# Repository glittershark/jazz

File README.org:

#+title: jazz

some daisy seed effect pedal firmware

run ~nix-shell~ to get dependencies. see [[https://github.com/glittershark/jazz/blob/main/shell.nix][shell.nix]] for a list of dependencies if
you are less of a nix weenie than i am

* building and testing

be sure to check out all the submodules:
#+begin_src shell-session
$ git submodule update --init --recursive
#+end_src

to build firmware blobs for all effects:

#+begin_src shell-session
$ make
#+end_src

to run tests:

#+begin_src shell-session
$ make test
#+end_src

~compile_commands.json~ is automatically merged from both ARM and host builds into the project root for clangd/language server support.

* host audio CLI

for quick iteration without flashing firmware, the host CLI lets you run effects
on mp3 files from your computer.

** quick start

build the host CLI:

#+begin_src shell-session
$ make console
#+end_src

run input through the default effect (~granular~) and play through your computer:

#+begin_src shell-session
$ ./build-test/src/console/jazz-console input.mp3
#+end_src

save processed output to a new mp3:

#+begin_src shell-session
$ ./build-test/src/console/jazz-console input.mp3 --output processed.mp3
#+end_src

output filenames default to the ~mp3s/~ folder in the current directory (created
if needed), so this writes ~mp3s/processed.mp3~ when run from the repo root.
explicit paths such as ~./processed.mp3~ or ~/tmp/processed.mp3~ are used as given.

if the output already exists, choose ~n~ to append the first available number
(~processed_1.mp3~, ~processed_2.mp3~, ...), ~o~ to overwrite, or ~c~ to cancel.
Enter or end-of-input cancels with a nonzero exit status before playback or
rendering starts. overwriting the input file itself is rejected; choose a
numbered filename instead.

if playback fails on your machine, disable playback and render offline:

#+begin_src shell-session
$ ./build-test/src/console/jazz-console input.mp3 --no-play --output processed.mp3
#+end_src

** effects and chains

list available effects:

#+begin_src shell-session
$ ./build-test/src/console/jazz-console --list-effects
#+end_src

select one effect:

#+begin_src shell-session
$ ./build-test/src/console/jazz-console input.mp3 --effect clip
#+end_src

try the fridge terminal preset:

#+begin_src shell-session
$ ./build-test/src/console/jazz-console input.mp3 --preset presets/host/fridge_demo.toml --output fridge_demo.mp3
#+end_src

try the standalone la sort demo (the same sorting engine runs on the Daisy):

#+begin_src shell-session
$ ./build-test/src/console/jazz-console input.mp3 --preset presets/host/la_sort_demo.toml --output la_sort_demo.mp3
#+end_src

add ~--no-play~ to render offline. for a fully wet version or a different rank:

#+begin_src shell-session
$ ./build-test/src/console/jazz-console input.mp3 --preset presets/host/la_sort_demo.toml --la-sort-dry 0 --la-sort-wet 1 --la-sort-weight-center 0.65
#+end_src

la sort keeps the MP3's left and right channels separate. see
[[file:src/la_sort/README.md][the la sort guide]] for controls and firmware details.

inspect the fridge preset's LFO motion without rendering audio:

#+begin_src shell-session
$ ./build-test/src/console/jazz-console --preset presets/host/fridge_demo.toml --fridge-lfo-chart
#+end_src

render that LFO motion as a matplotlib image:

#+begin_src shell-session
$ python scripts/plot_fridge_lfo.py --preset presets/host/fridge_demo.toml --output fridge_lfo.png
#+end_src

chain multiple effects in order:

#+begin_src shell-session
$ ./build-test/src/console/jazz-console input.mp3 --effect clip,lowpass,granular
#+end_src

** effect parameters

you can tune parameters from the command line:

#+begin_src shell-session
$ ./build-test/src/console/jazz-console input.mp3 --effect clip,la_sort --clip-threshold 0.2 --la-sort-weight-center 0.65
#+end_src

supported parameter flags:
- ~--clip-threshold~, ~--clip-gain~
- ~--anticlip-threshold~, ~--anticlip-gain~
- ~--lowpass-alpha~, ~--highpass-alpha~
- ~--cursed-lowpass-alpha~, ~--cursed-highpass-alpha~
- ~--la-sort-weight-center~, ~--la-sort-weight-sharpness~
- ~--la-sort-dry~, ~--la-sort-wet~
- ~--la-sort-length~: integer 1–1024 samples, default 64; preset key ~la_sort_length~
- ~--la-sort-volume-compensation~: 0–1, default 1; fixed sqrt(length) wet gain, up to +30 dB at 1024 (no dynamics control)
- ~--la-sort-lfo-rate~: 0.05–20 Hz, default 1; ~--la-sort-lfo-depth~: 0–1, default 0 (off), 1 sweeps the whole list

the fridge effect is configured through preset keys with the prefixes
~fridge_head_N_~ and ~fridge_lfo_N_~; see ~presets/host/fridge_demo.toml~.

** presets (toml/json)

load a preset file:

#+begin_src shell-session
$ ./build-test/src/console/jazz-console input.mp3 --preset presets/host/clip_lasort.toml --output processed.mp3
#+end_src

example presets included in repo:
- ~presets/host/fridge_demo.toml~
- ~presets/host/la_sort_demo.toml~
- ~presets/host/clip_lasort.toml~

CLI flags override preset values, so you can start from a preset and tweak:

#+begin_src shell-session
$ ./build-test/src/console/jazz-console input.mp3 --preset presets/host/clip_lasort.toml --clip-threshold 0.1
#+end_src

JSON preset example:

#+begin_src shell-session
$ cat > /tmp/example_preset.json <<'EOF'
{
  "effect_chain": ["clip", "la_sort", "highpass"],
  "clip_threshold": 0.3,
  "clip_gain": 10.0,
  "la_sort_weight_center": 0.62,
  "la_sort_weight_sharpness": 4.0,
  "highpass_alpha": 0.2
}
EOF
$ ./build-test/src/console/jazz-console input.mp3 --preset /tmp/example_preset.json --output processed.mp3
#+end_src

the CLI depends on ~ffmpeg~ and ~ffplay~ being available in your shell.

* flashing to daisy seed

to flash a particular effect to a daisy seed via STLink:

#+begin_src shell-session
$ make flash DIR=delay
#+end_src

or manually:

#+begin_src shell-session
$ st-flash write build/src/delay/delay.bin 0x08000000
$ st-flash reset
#+end_src

* printing stuff

see [[https://github.com/glittershark/jazz/blob/main/src/console/console.cpp][console]] for how to set up the console. reading from it should be something
like ~screen /dev/ttyACM0 115200~.

* current effects

** delays
- [[https://github.com/glittershark/jazz/blob/main/src/delay/delay.cpp][delay]]: literally just a perfectly clean delay.
- [[https://github.com/glittershark/jazz/blob/main/src/reverse/reverse.cpp][reverse]]: a simple reverse delay.
- [[https://github.com/glittershark/jazz/blob/main/src/granular/granular.cpp][granular]]: weird semi-generative granular delay.
- [[https://github.com/glittershark/jazz/tree/main/src/rachel][rachel]]: heavily modulated multi-delay

** filters
- [[https://github.com/glittershark/jazz/blob/main/src/low_pass_filter/lowpass_filter.cpp][low_pass_filter]]: simple one-pole lowpass filter.
- [[https://github.com/glittershark/jazz/blob/main/src/high_pass_filter/highpass_filter.cpp][high_pass_filter]]: simple one-pole highpass filter.
- [[https://github.com/glittershark/jazz/blob/main/src/cursed_low_pass_filter/cursed_lowpass_filter.cpp][cursed_low_pass_filter]]: cursed lowpass filter using exponentiation and multiplication.
- [[https://github.com/glittershark/jazz/blob/main/src/cursed_high_pass_filter/cursed_highpass_filter.cpp][cursed_high_pass_filter]]: cursed highpass filter using exponentiation and multiplication.

** distortion
- [[https://github.com/glittershark/jazz/blob/main/src/clip/clip.cpp][clip]]: hard clipping distortion.
- [[https://github.com/glittershark/jazz/blob/main/src/anticlip/anticlip.cpp][anticlip]]: adds back the residue from clipping.

** other
- [[file:src/la_sort/README.md][la_sort]]: stereo sorting-based effect with a weighted tap from a configurable rolling window (default 64 samples), shared by firmware and the MP3 demo.

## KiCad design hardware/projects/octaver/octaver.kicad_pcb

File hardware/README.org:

#+title: README (hardware)

* directory structure
- =projects/=: kicad projects
  - =devboard/=: general development board
  - =octaver/=: the can
- =lib/=: library files
  - =kicad/=: kicad part library files
    - =custom.kicad_sym=: custom symbol library (stuff we've drawn)
    - =custom.pretty/=: custom footprint library (stuff we've drawn)
    - =vendor/=: symbol library files (=*.kicad_sym=) downloaded from vendors
    - =vendor.pretty/=: footprint files (=*.kicad_mod=) & 3D models downloaded from vendors
  - =spice/=: spice simulation files
* creating a new project
1. create it in kicad under =projects/=
2. copy == & == from this directory into the project; this pulls in our custom
   libraries with all our stuff
3. enjoy!
* adding downloaded symbols & footprints
1. download the symbol & footprint libraries for the latest version of kicad
   available (6+ is fine)
2. move files:
   a. =*.kicad_sym= -> =lib/kicad/vendor/=
   b. =*.kicad_mod=, 3D models -> =lib/kicad/vendor.pretty/=
3. open the symbol editor. for each new symbol, change the footprint reference
   to =vendor:*= (since we just put the footprint into our own library)
4. open the footprint editor: for each new referenced footprint, if it should
   have a 3D model associated with it (i.e., the library came with a model),
   ensure the model shows up in the 3D view of the footprint. if not, add it and
   move it to the right place.

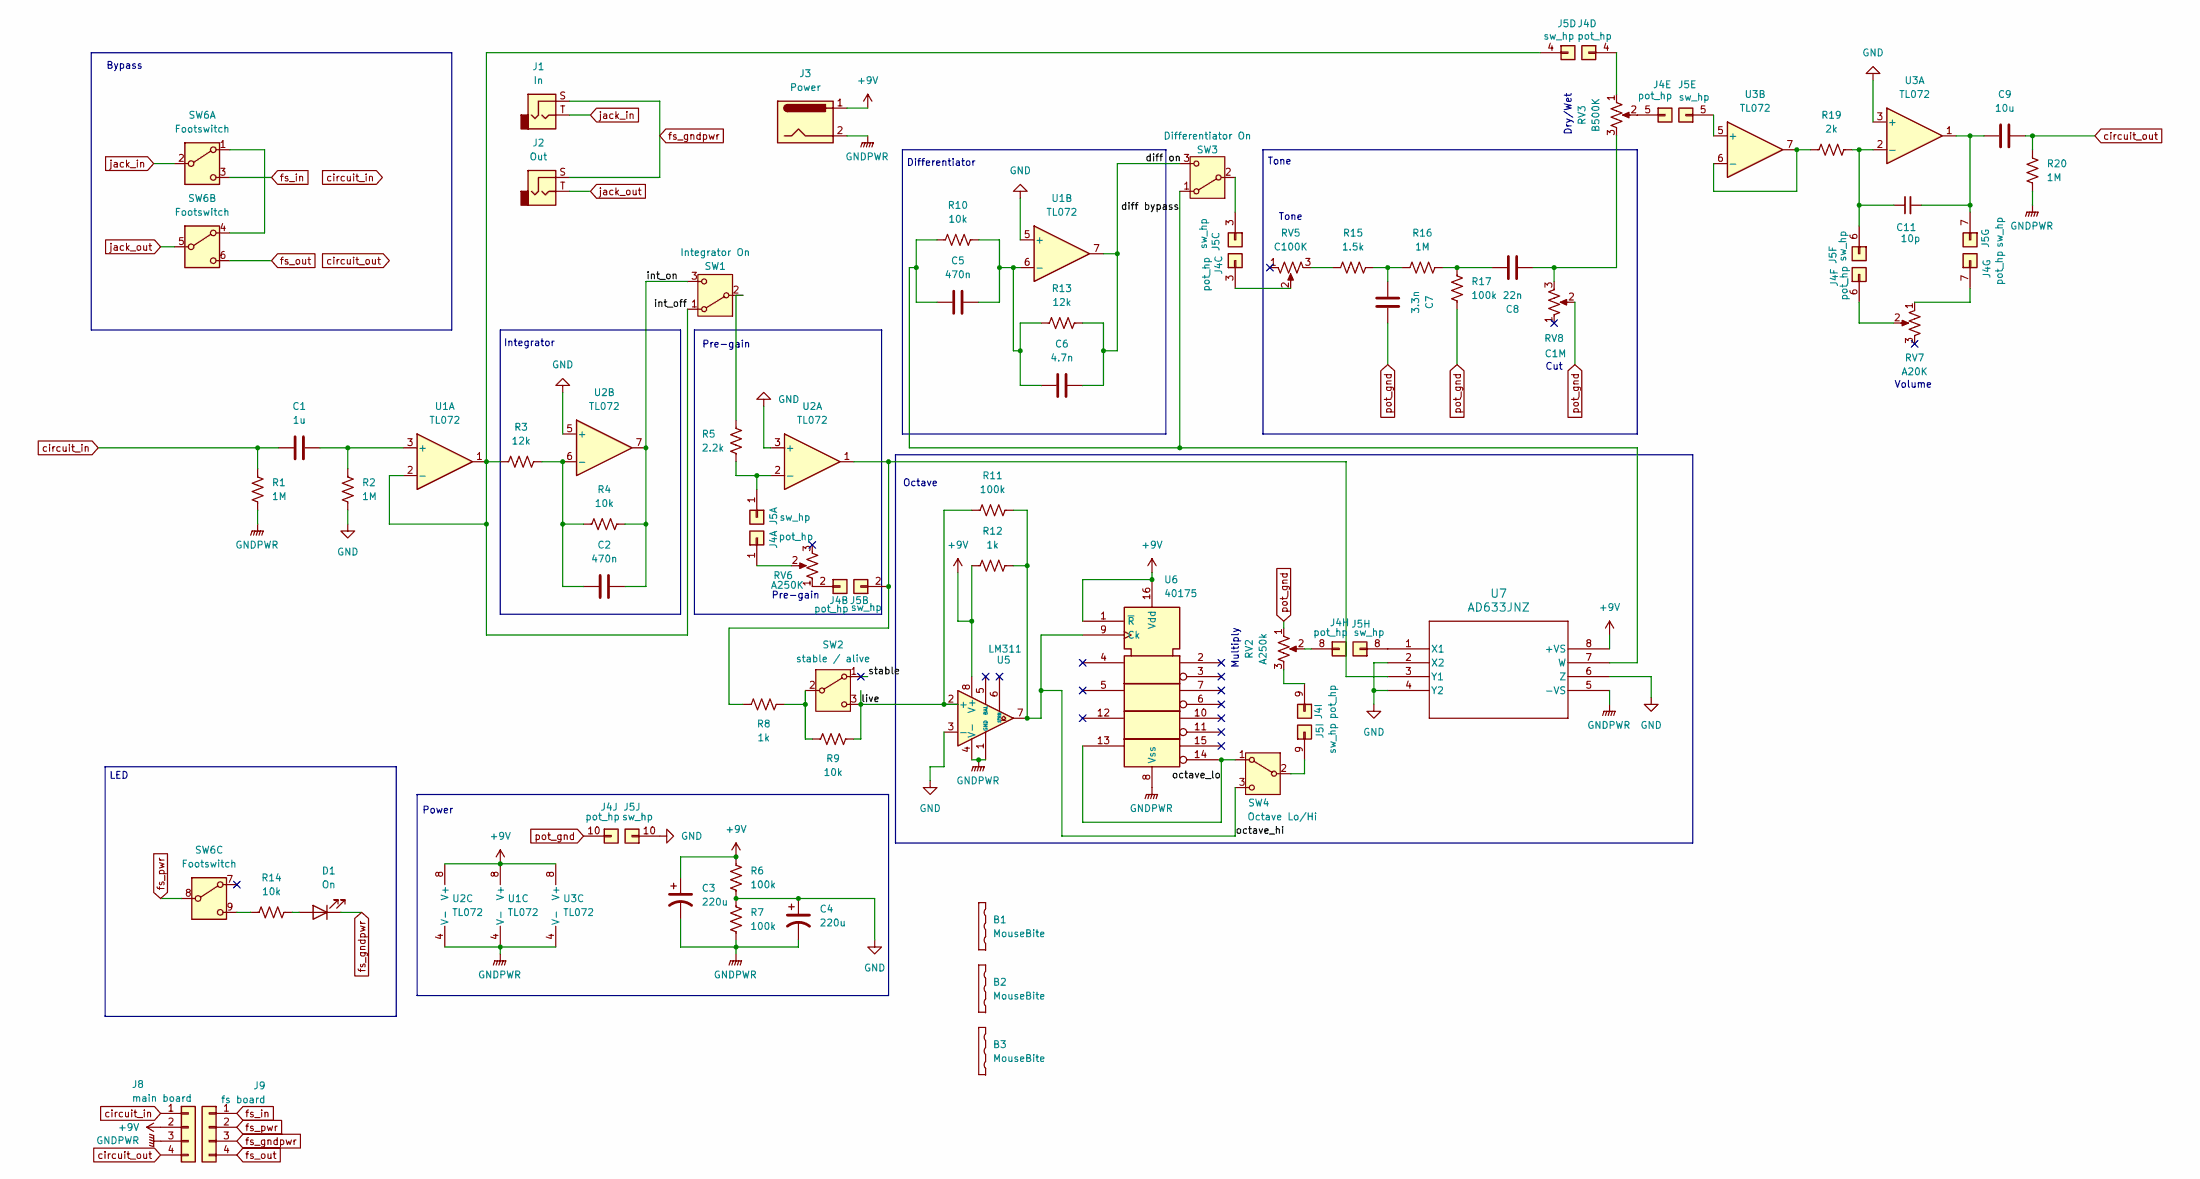
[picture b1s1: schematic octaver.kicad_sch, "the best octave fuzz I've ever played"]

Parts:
B1, B2, B3: MouseBite; MouseBite_2.54x7.62mm_JLCPCB
C1: 1u; C_0603_1608Metric; LCSC C15849
C2, C5: 470n; C_0603_1608Metric; LCSC C1623
C3, C4: 220u; CP_Elec_8x10.5; LCSC C3340
C6: 4.7n; C_0603_1608Metric; LCSC C53987
C7: 3.3n; C_0603_1608Metric; LCSC C1613
C8: 22n; C_0603_1608Metric; LCSC C21122
C9: 10u; C_0603_1608Metric; LCSC C96446
C11: 10p; C_0603_1608Metric; LCSC C1634
D1: On; LED_D5.0mm
J1: In; mono_jack
J2: Out; mono_jack
J3: Power; PinHeader_1x02_P2.54mm_Vertical
J4: pot_hp; PinHeader_1x10_P2.54mm_Vertical
J5: sw_hp; PinHeader_1x10_P2.54mm_Vertical
J8: main board; PinHeader_1x04_P2.54mm_Vertical
J9: fs board; PinHeader_1x04_P2.54mm_Vertical
R1, R2, R16, R20: 1M; R_0402_1005Metric; LCSC C26083
R3, R13: 12k; R_0402_1005Metric; LCSC C25752
R4, R9, R10: 10k; R_0402_1005Metric; LCSC C25744
R5: 2.2k; R_0402_1005Metric; LCSC C25879
R6, R7, R11, R17: 100k; R_0402_1005Metric; LCSC C25741
R8, R12: 1k; R_0402_1005Metric; LCSC C11702
R14: 10k; R_Axial_DIN0207_L6.3mm_D2.5mm_P10.16mm_Horizontal
R15: 1.5k; R_0402_1005Metric; LCSC C25867
R19: 2k; R_0402_1005Metric; LCSC C4109
RV2: A250k; Taiss_Potentiometer_vertical
RV3: B500K; Taiss_Potentiometer_vertical
RV5: C100K; Taiss_Potentiometer_vertical
RV6: A250K; Taiss_Potentiometer_vertical
RV7: A20K; Taiss_Potentiometer_vertical
RV8: C1M; Taiss_Potentiometer_vertical
SW1: Integrator On; Adam Tech SW-T3-2B-A-A3-S1
SW2: stable / alive; Adam Tech SW-T3-2B-A-A3-S1
SW3: Differentiator On; Adam Tech SW-T3-2B-A-A3-S1
SW4: Octave Lo/Hi; Adam Tech SW-T3-2B-A-A3-S1
SW6: Footswitch; PBS-24-302_3PDT
U1, U2, U3: TL072; SOIC-8_3.9x4.9mm_P1.27mm; LCSC C6961
U5: LM311; SOIC-8_3.9x4.9mm_P1.27mm; LCSC C7939
U6: 40175; SOIC-16W_5.3x10.2mm_P1.27mm; LCSC C1549824
U7: AD633JNZ; DIP-8_W7.62mm

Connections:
+9V: C3.1, J3.1, J8.2, R6.2, R12.2, U1.8 (V+), U2.8 (V+), U3.8 (V+), U5.8 (V+), U6.1 (~R), U6.16 (Vdd), U7.8 (+VS)
/diff bypass: C5.2, R10.2, SW3.1 (A), U7.7 (W)
/diff on: C6.1, R13.1, SW3.3 (C), U1.7
/int_off: J5.4 (Pin_3), R3.2, SW1.1 (A), U1.1, U1.2 (-)
/int_on: C2.1, R4.1, SW1.3 (C), U2.7
/live: R9.2, R11.2, SW2.3 (C), U5.2 (+)
/octave_hi: R11.1, R12.1, SW4.3 (C), U5.7, U6.9 (Ck)
/octave_lo: SW4.1 (A), U6.13, U6.14
/stable: SW2.1 (A)
GND: C4.1, J5.10 (Pin_3), R2.1, R6.1, R7.2, U1.5 (+), U2.3 (+), U2.5 (+), U3.3 (+), U5.3 (-), U7.2 (X2), U7.4 (Y2), U7.6 (Z)
GNDPWR: C3.2, C4.2, J3.2, J8.3, R1.1, R7.1, R20.1, U1.4 (V-), U2.4 (V-), U3.4 (V-), U5.1 (GND), U5.4 (V-), U6.8 (Vss), U7.5 (-VS)
unnamed: C7.2, R15.1, R16.2
unnamed: C8.1, R16.1, R17.2
unnamed: C8.2, RV3.3, RV8.3
unnamed: D1.2 (A), R14.1
unnamed: J4.1 (Pin_3), RV6.2
unnamed: J4.2, RV6.1
unnamed: J4.3, RV5.2
unnamed: J4.4 (Pin_3), RV3.1
unnamed: J4.5 (Pin_3), RV3.2
unnamed: J4.6 (Pin_3), RV7.2
unnamed: J4.7 (Pin_3), RV7.1
unnamed: J4.8 (Pin_3), RV2.2
unnamed: J4.9 (Pin_3), RV2.3
unnamed: J5.1 (Pin_3), R5.1, U2.2 (-)
unnamed: J5.2, R8.1, U2.1, U7.3 (Y1)
unnamed: J5.3, SW3.2 (B)
unnamed: J5.5 (Pin_3), U3.5 (+)
unnamed: C11.1, J5.6 (Pin_3), R19.1, U3.2 (-)
unnamed: C9.2, C11.2, J5.7 (Pin_3), U3.1
unnamed: J5.8 (Pin_3), U7.1 (X1)
unnamed: J5.9 (Pin_3), SW4.2 (B)
unnamed: R15.2, RV5.3
unnamed: R5.2, SW1.2 (B)
unnamed: R8.2, R9.1, SW2.2 (B)
unnamed: SW6.1 (A), SW6.4 (A)
unnamed: R14.2, SW6.9 (C)
unnamed: C1.1, R2.2, U1.3 (+)
unnamed: C5.1, C6.2, R10.1, R13.2, U1.6 (-)
unnamed: C2.2, R3.1, R4.2, U2.6 (-)
unnamed: R19.2, U3.6 (-), U3.7
circuit_in: C1.2, J8.1, R1.2
circuit_out: C9.1, J8.4, R20.2
fs_gndpwr: D1.1 (K), J1.S, J2.S, J9.3
fs_in: J9.1, SW6.3 (C)
fs_out: J9.4, SW6.6 (C)
fs_pwr: J9.2, SW6.8 (B)
jack_in: J1.T, SW6.2 (B)
jack_out: J2.T, SW6.5 (B)
pot_gnd: C7.1, J4.10 (Pin_3), R17.1, RV2.1, RV8.2

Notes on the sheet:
Pre-gain
Power
Differentiator
Volume
Octave
Tone
Dry/Wet
Bypass
Cut
LED
Multiply
Integrator

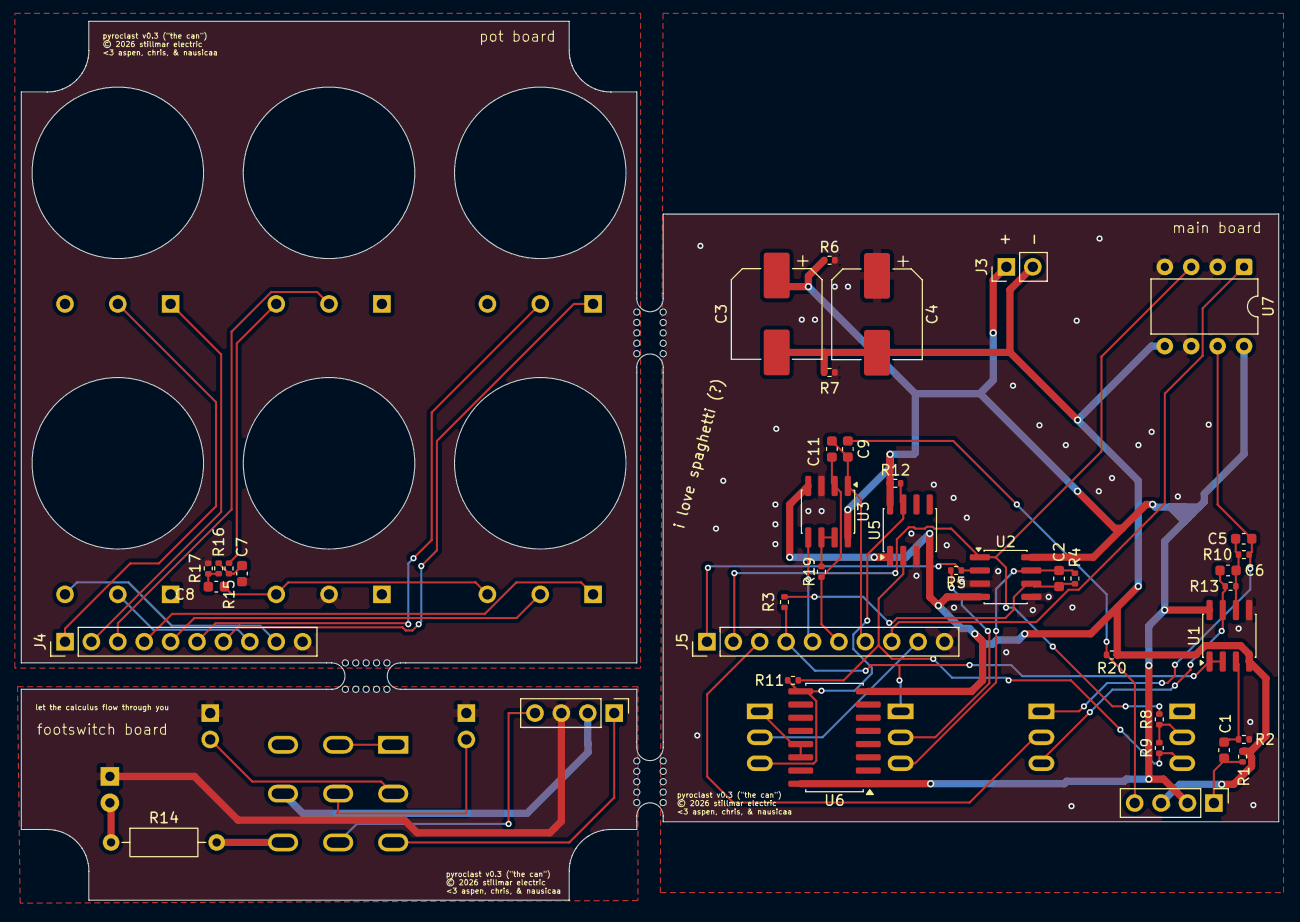
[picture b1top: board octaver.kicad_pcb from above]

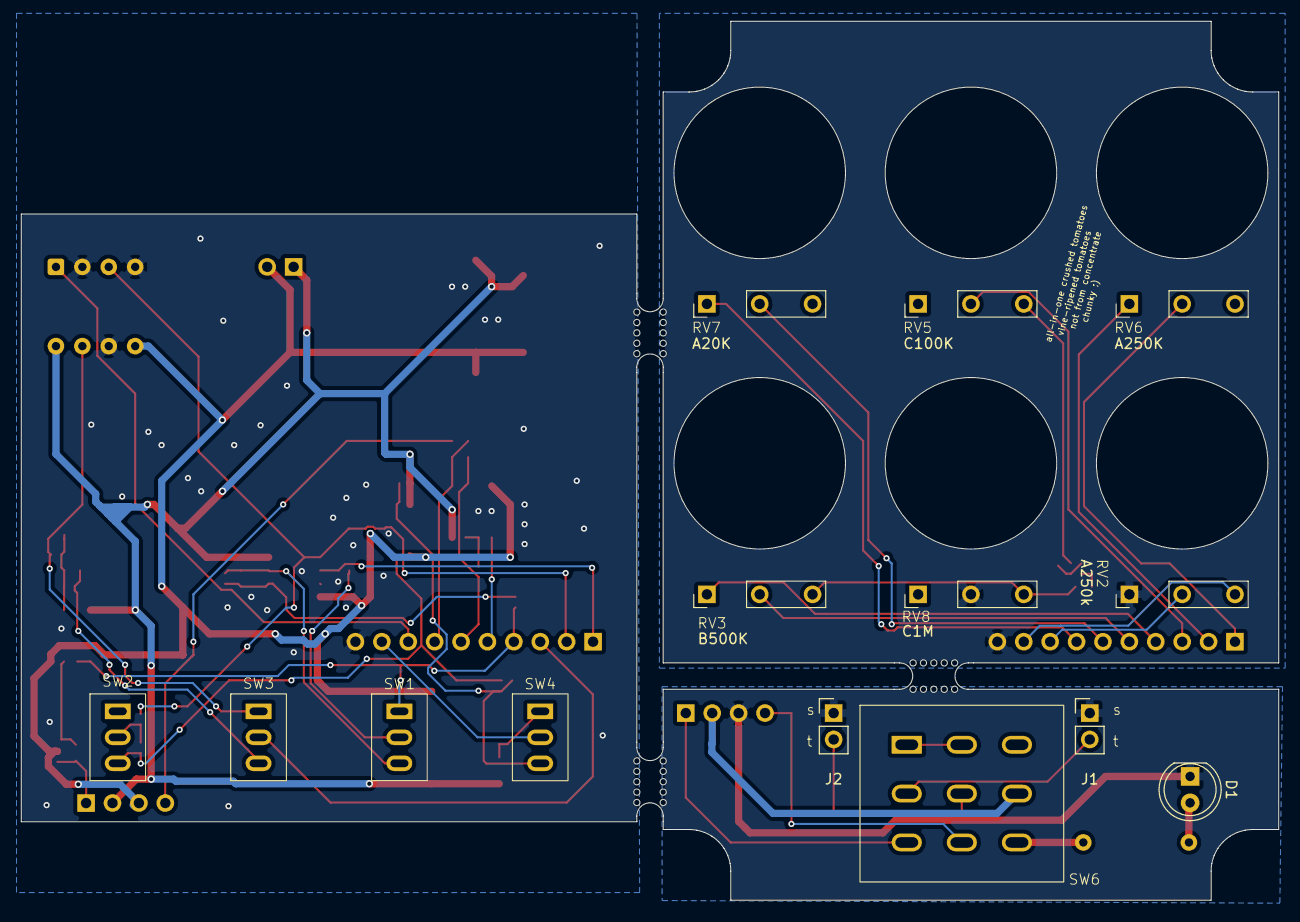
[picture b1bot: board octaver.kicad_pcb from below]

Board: 2 copper layers, 121.0 x 84.5 mm, 57 parts (14 on the bottom side), 49 nets.

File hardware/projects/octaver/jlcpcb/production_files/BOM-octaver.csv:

Comment,Designator,Footprint,LCSC,Quantity
1.5k,R15,R_0402_1005Metric,C25867,1
100k,"R11,R17,R6,R7",R_0402_1005Metric,C25741,4
10k,"R10,R4,R9",R_0402_1005Metric,C25744,3
10p,C11,C_0603_1608Metric,C1634,1
10u,C9,C_0603_1608Metric,C96446,1
12k,"R13,R3",R_0402_1005Metric,C25752,2
1M,"R1,R16,R2,R20",R_0402_1005Metric,C26083,4
1k,"R12,R8",R_0402_1005Metric,C11702,2
1u,C1,C_0603_1608Metric,C15849,1
2.2k,R5,R_0402_1005Metric,C25879,1
220u,"C3,C4",CP_Elec_8x10.5,C3340,2
22n,C8,C_0603_1608Metric,C21122,1
2k,R19,R_0402_1005Metric,C4109,1
3.3n,C7,C_0603_1608Metric,C1613,1
4.7n,C6,C_0603_1608Metric,C53987,1
40175,U6,SOIC-16W_5.3x10.2mm_P1.27mm,C1549824,1
470n,"C2,C5",C_0603_1608Metric,C1623,2
LM311,U5,SOIC-8_3.9x4.9mm_P1.27mm,C7939,1
TL072,"U1,U2,U3",SOIC-8_3.9x4.9mm_P1.27mm,C6961,3

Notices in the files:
hardware/projects/devboard/devboard.kicad_pcb:
© 2026 stillmar electric
